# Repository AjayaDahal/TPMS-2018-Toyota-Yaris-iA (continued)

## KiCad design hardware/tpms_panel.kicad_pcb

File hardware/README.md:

# TPMS Monitor Panel: KiCad project

> **Outline accepted from the in-car paper fit (2026-11-09).** The 1:1 template matched the console opening under the HVAC controls, so the board was built to that outline, shrunk by 1 mm on the left, right and bottom edges so it can't come out too big.
> Any small gaps can be closed later with a 3D-printed bezel or chassis.
> `production/tpms_panel_gerbers_jlcpcb.zip` is the order file. The USB holes are Ø25.8 mm, sized for your passthrough sockets' measured 25.16 mm (M25-class) thread.
> The latest design audit is in [docs/design_audit.md](docs/design_audit.md).

This is the hardware for the 315 MHz TPMS display described in the project report
([../TPMS_project_report_ECE6723.pdf](../TPMS_project_report_ECE6723.pdf)). The board outline and front
layout follow Figure 3.6 of the report. The whole project is generated by a script, so you can
change the dimensions and rebuild it (see section 7).

| Front (display side) | Back (electronics) |
|---|---|
|  |  |

## 1. Review: will the documented receiver (MX-05V / XY-MK-5V) work?

**The sensor.** The FCC report in your appendix is for the GM/Schrader **EG53MA4** (FCC ID MRXEG53MA4). These are the four sensors installed in the car's tyres; the Yaris iA's own TPMS is indirect and uses no wheel sensors. Key specs:
- 315 MHz ±70 kHz, **ASK/OOK**, Manchester coded.
- Half-bit pulses are about **123 µs**, so roughly 8 kBd on air and ~4 kbit/s of data.
- Each frame lasts 13–28 ms.
- It sends every 30–60 s while the wheels turn, and nothing while the car is parked unless you trigger it with the LF relearn tool.

At 3 m the FCC measured a peak field strength of 78.4 dBµV/m, which is about −49 dBm into an isotropic antenna. Inside a car you can expect roughly −60 to −80 dBm. That is plenty for both receivers, so sensitivity is not the problem. The real limits are listed below.

| | MX-05V superregenerative (documented) | CC1101 module (purchased) |
|---|---|---|
| Modulation | OOK only | OOK/ASK, 2-FSK, GFSK, 4-FSK, MSK. Also covers the FSK sensors used by Toyota, Ford and many aftermarket brands |
| Selectivity | Very wide (MHz-range) front end. Key fobs and any nearby 300–330 MHz traffic get through | Programmable RX filter (e.g. 203 kHz) and a crystal-referenced synthesizer |
| Frequency stability | Tuned by a trimmer coil that drifts with temperature and vibration (car interior: −20…+70 °C) | Crystal accurate (tens of ppm) |
| Idle output | No squelch, so the DATA pin outputs constant noise. The MCU must reject it all the time | Carrier-sense/RSSI available on GDO2, so the MCU can ignore idle noise |
| ~123 µs Manchester | Marginal: these modules are designed for slow (a few kbit/s) remotes, and the LM358 slicer distorts short pulses | Handled easily |
| Supply / logic | 5 V | 3.3 V only (1.8–3.6 V, not 5 V tolerant) |

**Verdict: the MX-05V is not suitable for the in-car panel. Use the CC1101.**
- On the bench it can be a proof of concept with your GM sensors, but only if it is the **315 MHz** version; the 433 MHz one won't hear them.
- In the car, expect missed and corrupted frames, for the reasons in the table above.
- The PCB keeps an optional, unpopulated socket for it (J3, with R9/R10 as a 5 V→3.3 V divider), only for a side-by-side comparison. Leave J3, R9 and R10 empty.

**Your actual module (from the photos): EBYTE E07-M1101D(-SMA) V2.0**
- **Nothing is missing.** The E07 has an 8-pin 2×4 header and all 8 pins are present; pin 1 is the square pad. The green 10-pin CC1101 boards only add a second VCC and GND.
- **The PCB already fits it.** EBYTE's pin table (1 GND, 2 VCC, 3 GDO0, 4 CSN, 5 SCK, 6 MOSI, 7 MISO, 8 GDO2) and size (15 × 30 mm without the SMA) match the U1 footprint, so the PCB needs no change.
- **It is the 433 MHz build.**
  - The silkscreen says "433M" and EBYTE rates the module for 387–464 MHz.
  - The CC1101 chip tunes to 300–348 MHz, so it can receive the 315 MHz sensors. However, the RF matching parts between the chip and the SMA are tuned for 433 MHz, so it loses some sensitivity at 315 MHz (rough estimate: up to ~10 dB).
  - It should still work. The car gives about −60 to −80 dBm (see above), and the CC1101 needs roughly −100 dBm at this data rate (EBYTE quotes −108 dBm at 0.6 kbps).
- **Use a 315 MHz antenna.** An antenna sold with a 433 MHz module is also tuned for 433 MHz. A 315 MHz SMA whip, or for a quick test a ~23 cm wire on the SMA centre pin, recovers part of the loss. Keep the antenna away from metal. An SMA extension cable lets you put it behind plastic trim and keeps its weight off the module's header in a vibrating car.
- **Bring-up checks:**
  1. Continuity from pin 1 to the SMA outer shell should beep (GND).
  2. Over SPI, read the VERSION status register (0x31, sent as 0xF1).
     - 0x14 (current) or 0x04 (legacy) means a TI CC1101.
     - 0x17 or 0x03 means a known clone chip; RadioLib accepts these and they usually work.
     - 0x00 or 0xFF means the wiring/SPI is wrong.
  3. Check that every tyre's frames arrive with an RSSI well above the idle noise floor, and compare against your RTL-SDR running rtl_433.
- **About "TI" and "clone":** TI makes only the chip. The module is EBYTE's own Chinese design, so a Chinese board is expected and does not by itself mean a fake. Check 2 shows whether the chip is genuine.
- **If the rear tyres drop out:**
  - Use a module built for 315 MHz, or re-tune its RF parts to the 315 MHz values in TI's CC1101 reference design.
  - If the replacement's pinout differs from the E07, wire it to the **J2** 1×8 breakout (GND 3V3 GDO0 CSN SCK MOSI MISO GDO2) instead of U1.

## 2. Microcontroller: ESP32 (DOIT ESP32 DEVKIT V1, 30-pin)

| | Arduino Nano | STM32 Blue Pill | **ESP32 DevKit V1** |
|---|---|---|---|
| Logic level | 5 V (needs level shifters for CC1101 and OLED) | 3.3 V | **3.3 V**, matches CC1101 and OLED |
| RAM | 2 KB, which can't even hold the 4 KB 128×64×4-bit OLED frame buffer | 20 KB | **520 KB** |
| CPU | 16 MHz AVR | 72 MHz M3 | **2×240 MHz** (decoding + UI) |
| Wireless | none | none | **Wi-Fi + BLE**: phone app, OTA updates, logging |
| Notes | | clone MCUs common, needs ST-Link | USB bootloader, hardware pulse counter for the encoder, enough GPIO for display, LEDs and expansion |

Both DOIT variants are sold: **0.9 in (22.86 mm)** and **1.0 in (25.4 mm)** row spacing. The footprint provides both GPIO23…3V3 rows. Populate only the row that matches your board.

## 3. Board summary

- **Outline:**
  - Trapezoid, 189 mm wide at the top, 121 mm at the bottom and 128 mm tall. That is the console opening the paper template matched in the car (191 × 123 × 129 mm), minus 1 mm on the left, right and bottom edges.
  - **USB cable slot** in the right edge: 8 mm wide, 8 mm deep, centred 34 mm below the top. The cable from the car's own USB port, which ends up behind the panel, comes out through it.
  - Two Ø25.8 mm cut-outs for the panel-mount USB passthroughs (measured thread 25.16 mm, M25 class), plus 4× M3 holes.
    - No parts within Ø38 mm on either side of each hole, so an M25 nut (typically 35–37 mm across corners) sits flat. DRC checks this.
    - No tracks within Ø31 mm, so a hole could still be drilled out to Ø30 mm.
    - The mounting holes are placeholders; move or delete them in `panel_config.py`.
  - The shape started as a scale-up of Figure 3.6 (using the 82 mm-wide display as the reference). It was then checked in the car with the 1:1 paper template, and a caliper span along the left trim agreed with it.
- **Front:**
  - NHD-2.7-12864WDW3 OLED (SSD1322, 4-wire SPI).
  - 4× 5 mm tyre LEDs centred under the display in a 2×2 "car" layout (FL FR / RL RR) with a car outline on the silkscreen between them.
  - EC11 rotary encoder with push switch to the right of the display: rotate = up/down, push = OK. BACK is a menu entry on the screen and/or a long-press.
  - The original 4-button layout (UP/OK/DOWN/BACK in a column on the right) is still available: set `INPUT_STYLE = "buttons"` in `scripts/panel_config.py` and rebuild.
- **Back:**
  - ESP32 DevKit (on sockets).
  - CC1101 module on the left, with its SMA connector pointing down so the antenna can go straight back into the console pocket.
  - 12 V ACC input: PTC fuse, ±22 V TVS (SMAJ22CA) and SS34 reverse diode, then a TSR 1-2450 5 V switcher, then an AMS1117 3.3 V LDO with a copper heatsink pour (feeds the OLED and radio).
  - Buzzer driver, optional MX-05V socket, optional CC1101 breakout, I²C/GPIO expansion header.
- **PCB:** 2 layers, 1.6 mm, 1 oz copper, GND pour on both sides with stitching vias, tented vias. Rules: 0.25 mm signal / 0.6 mm power tracks, 0.2 mm clearance, 0.6/0.3 mm vias. DRC also enforces JLCPCB's silkscreen limits (text ≥ 1.0 mm high, ≥ 0.15 mm stroke), via ring ≥ 0.15 mm and hole-to-hole ≥ 0.45 mm.
- **Checks (KiCad 10.0.7):**
  - ERC: 0 errors / 0 warnings.
  - DRC: 0 errors / 0 warnings / 0 unconnected.
  - Schematic ↔ PCB parity: 0 issues.
  - The exported Gerber/drill files were also re-read with an independent parser: outline closed (189 × 128 mm, with the 8 mm cable slot), every plated hole has a pad on both layers, no copper on non-plated holes. See [docs/design_audit.md](docs/design_audit.md).

### ESP32 pin map

| GPIO | Net | Connected to |
|---|---|---|
| IO18 / IO23 / IO19 | SPI_SCK / SPI_MOSI / SPI_MISO | CC1101 and OLED (shared VSPI bus; the OLED is write-only) |
| IO5 | CC_CS | CC1101 CSn |
| IO34 | CC_GDO0 | CC1101 GDO0: demodulated OOK data (use an edge interrupt) |
| IO35 | CC_GDO2 | CC1101 GDO2: e.g. carrier sense |
| IO15 / IO27 / IO26 | OLED_CS / OLED_DC / OLED_RES | NHD pins 17 / 4 / 16 |
| IO25 / IO33 / IO32 / IO14 | LED_FL / FR / RL / RR | LEDs through 220 Ω (active high) |
| IO16 / IO17 / IO4 | ENC_A / ENC_B / ENC_SW | Encoder A/B through 10 k pull-up + 10 k / 10 nF RC filter (use the ESP32 PCNT unit or interrupts); push switch with 10 k pull-up + 100 nF (active low) |
| IO13 | BUZZER | MMBT3904 driving a 5 V buzzer (active high) |
| IO36 | MX05_DATA | Optional MX-05V through a 1 k / 10 k divider (its LM358 output reaches only ~3.0–3.7 V, so this gives 2.7–3.4 V) |
| IO21 / IO22 | I2C_SDA / I2C_SCL | J4 expansion, 4.7 k pull-ups |
| IO2 | IO2_EXP | J4 spare. Keep it low or floating at reset so flashing still works |
| IO39 | IO39_EXP | J4 spare, input-only (ADC1), e.g. a fifth button or a light sensor |

IO12 (boot-strapping pin), IO0, TX0/RX0 and EN are deliberately left unused.

## 4. Ordering at JLCPCB

1. Upload **`production/tpms_panel_gerbers_jlcpcb.zip`**. It contains Gerbers, separate PTH/NPTH Excellon drill files and drill maps.
   - If `DIMENSIONS_CONFIRMED` is ever set back to `False`, the build names the zip `..._DRAFT_dims_unconfirmed.zip` instead. Don't order a DRAFT zip.
2. Options:
   - 2 layers, 1.6 mm, 1 oz.
   - **PCB colour: Black, silkscreen: White** (to match the render). ENIG looks nicer on a front panel than HASL.
   - Via covering: Tented.
   - "Remove order number": **Specify a location**. The `JLCJLCJLCJLC` marker is already on the back silkscreen, so the front stays clean.
3. The board is larger than 100×100 mm, so the low-cost promo price doesn't apply.

`production/tpms_panel_bom.csv` lists every part with suggested part numbers. Lines marked "optional" are only needed for the MX-05V test, the alternative CC1101 wiring, or future expansion.

## 5. Assembly notes

1. **Back, SMD first:** 1206 R/C, SOT-223, SMA, SOD-123, SOT-23, 1812 fuse, 6.3 mm electrolytic, and the C5 tantalum (case A). **C5 is polarized:** its banded end is "+" and goes on pad 1, the end closed off by the silkscreen bracket.
2. **Back, through-hole:**
   - TSR 1-2450 (U3). A substitute must also be a 7805-pinout switcher rated for at least 36 V input, e.g. Mornsun K7805-1000R3 (8–36 V). The RECOM R-78E5.0-1.0 is only rated 8–28 V, so don't use it here.
   - J1 screw terminal and the buzzer.
   - The ESP32 sockets: two 1×15 female headers, in the EN…VIN row plus the GPIO23…3V3 row for your board's width.
   - The CC1101 2×4 female socket.
3. **Front:**
   - LEDs: the square pad is the cathode. The 220 Ω resistors give ~6 mA with red, amber or yellow LEDs. Blue or white LEDs (Vf ≈ 3 V) would only get ~1 mA and look dim; use 47–68 Ω for those.
   - Encoder: EC11 with push switch and a 20 mm D-shaft, fitted with a 20–25 mm knob. Solder the two mounting tabs as well; they take the force when the knob is pushed.
   - Display: 1×20 2.54 mm male header with **pin 1 (VSS, square pad) at the right end when looking at the front** (from the NHD rear-view drawing). If you want the display removable, use a female header.
   - Display hardware: the NHD mounting holes are Ø2.5 mm, so use **M2** screws (M2.5 won't pass through) with **M2 × 3 mm** spacers between the display and the PCB.
4. Before fitting the display, trim the ESP32 socket pins that come through to the front **to ≤ 1 mm**, because they sit under the display.
   - The display's own back carries parts up to ~2.1 mm tall (bezel tabs, FPC connector), and its flex cable runs over the lower socket row.
   - With 3 mm spacers this leaves about 0.9 mm of clearance.
5. The CC1101 module plugs in components-up (facing away from the PCB) with its SMA pointing **down**.
   - In the car, the panel's top edge sits directly under the HVAC controls, so nothing can leave through it. That's why the module was moved off the top-left corner.
   - Fit a **90° SMA adapter** (male–female) on the module and point the 315 MHz antenna straight back into the console pocket.
   - Or use an SMA extension cable (RG316/RG174, 0.3–1 m) to put the antenna somewhere better; see the antenna notes in section 8.
   - The ESP32's micro-USB plug points left toward J2. It has about 60 mm of free run, or about 35 mm if J2 is fitted. A short-bodied or 90° micro-USB cable helps, or flash over Wi-Fi (OTA) once the first firmware is in.
6. **JP1 stays open.** Close it only if you rework the NHD module to jumper option #1 (R4 open, R5 closed) so its OLED boost converter runs from 5 V.
   - At full brightness the OLED draws up to 345 mA (375 mA max) from the 3.3 V LDO, about 0.65 W of heat in U4. The board has a copper pour on U4's tab for this.
   - With option #1, the boost draws ~200 mA from 5 V instead and U4 stays cool. Consider it if the panel will sit in a hot dashboard with a mostly-lit screen.
7. Power:
   - Connect switched **12 V ACC** to J1 (expected draw < 0.5 A).
   - Tap ACC through an **add-a-fuse (1–2 A)** at the fuse box. The on-board PTC protects the board, not the wire.
   - **Never wire it to constant 12 V.** The panel draws about 1 W, which flattens a car battery in roughly two weeks.
   - On the bench, the ESP32's USB alone powers everything. A laptop port (500 mA) can brown out when the screen is bright and Wi-Fi is on, so use a powered hub or a 12 V supply if it resets.
   - Most DevKits have a VBUS diode, so 12 V and USB can be connected together. If yours doesn't, use one or the other.
8. **USB passthroughs:** the two holes take panel-mount USB passthrough cables, with a female socket in front and a male plug behind. They aren't wired to the board.
   - Plug one male end into the car's own USB port behind the panel; the front socket then works like the car's port (phone charging, CarPlay/Android Auto if your head unit has them).
   - Plug the other into a 12 V → USB charger in the car's 12 V socket behind the panel.
     - Use a low-profile ("flush") charger, because a long one sticks out toward the back of the panel.
     - The board's U3 can't power phones, so the charger is needed.
   - The car's ports face the panel. If a straight USB plug or the charger doesn't leave room for the panel to sit flush, use **90° USB-A adapters** (male–female) so the plugs lie flat. Leave some slack so the panel doesn't lever on the car's port.
   - The extension cables are USB 3.0, so they run as USB 2.0 on the car's USB 2.0 port; that's fine.
   - Route both cables down and away from the CC1101 antenna. With a phone connected and charging, the bring-up firmware's noise floor should stay near −100 dBm; if it rises, add clip-on ferrites to the cables near the plugs.
   - Mounting: the thread measures 25.16 mm (M25 class), so the holes are **Ø25.8 mm** (0.6 mm clearance, enough for JLCPCB's ±0.2 mm routing tolerance).
     - Nothing is placed within a Ø38 mm circle on either side, so the nut and flange sit flat.
     - The nearest part is U3 at 19.8 mm from the hole centre, so even a 39 mm nut (across corners) would fit.
   - If the thread binds, ease the hole with a round file (copper-free up to Ø30 mm).
   - The slot in the right edge stays free for an extra cable, such as the antenna extension or the 12 V feed.
9. **First power-up:**
   - Before plugging in the DevKit, CC1101 and display, power the bare board and measure 5 V and 3V3 on the J4 pads.
   - The CC1101's 2×4 header and the DevKit are symmetric, so a module rotated 180° gets reversed power. Check the "1"/"SMA" and "USB"/"ANTENNA" silkscreen first.
   - Then flash the [bring-up firmware](../firmware/bringup/README.md); its self-test checks every part.
10. **For the car (vibration):**
    - Use machined round-pin gold sockets for the DevKit, or solder it in.
    - Put a dab of RTV on the socketed modules.
    - Don't hang a heavy antenna on the module. Use a short stubby antenna on the 90° adapter, or an extension cable with the antenna fixed to the console.
    - Crimp ferrules on the J1 wires.

## 6. Firmware starting points

> The Yaris iA's own TPMS is indirect (ABS wheel speeds, no wheel sensors). The four GM/Schrader EG53MA4 sensors you had installed feed only this panel, so the settings below are the ones to use.
> The [bring-up firmware](../firmware/bringup/README.md) already uses them and decodes the sensors (ID, pressure, temperature). Risks and next steps are in [docs/premortem.md](../docs/premortem.md).

### CC1101 settings for the GM/Schrader EG53MA4

These values are calculated from the CC1101 datasheet formulas for a 26 MHz crystal. Treat them as a starting point and check them in TI SmartRF Studio, which also gives the ASK/OOK AGC settings. The bring-up firmware's OOK profile uses the same settings with a 16 kBd demodulator filter.

| Register | Value | Meaning |
|---|---|---|
| FREQ2/1/0 | 0x0C / 0x1D / 0x8A | 315.000 MHz (793 994 × 26 MHz / 2¹⁶) |
| MDMCFG4 / MDMCFG3 | 0x88 / 0x4B | RX bandwidth 203 kHz, data rate ≈ 8.2 kBd |
| MDMCFG2 | 0x30 | ASK/OOK, no sync word |
| PKTCTRL0 | 0x32 | Asynchronous serial mode |
| IOCFG0 / IOCFG2 | 0x0D / 0x0E | GDO0 = serial data out (to IO34), GDO2 = carrier sense (to IO35) |

How to decode:
1. Timestamp every edge on IO34.
2. Manchester-decode with a half-bit of about 123 µs.
3. Parse the frame as rtl_433's `schrader_EG53MA4` decoder does (`src/devices/schraeder.c`): a 120-bit frame with a 24-bit ID, pressure byte × 25 mbar, temperature byte in °F, and an additive checksum.
4. Trigger each wheel with the OEC-T5 tool to learn which ID belongs to FL/FR/RL/RR.

Libraries such as SmartRC-CC1101-Driver-Lib or RadioLib work on the ESP32.

315 MHz needs band-specific settings besides FREQ:
- TEST0 must be 0x0B below ~323 MHz, versus 0x09 at 433 MHz.
- SmartRC's `setMHZ(315.0)` sets TEST0 and FSCTRL0 for you.
- If you write the registers yourself, export the 315 MHz set from SmartRF Studio. Don't reuse a 433 MHz register dump with only FREQ changed.

Encoder: count A/B with the ESP32 PCNT peripheral (e.g. the ESP32Encoder library); an EC11 gives 4 counts per detent, so divide by 4 for one menu step per click. Use a short press for OK and a long press (~0.6 s) for BACK.

Things to watch in firmware:
- **GDO0 clock at power-up:** until IOCFG0 is written, the CC1101 outputs a 135 kHz clock on GDO0 (its reset default, CLK_XOSC/192). Configure the radio first, then attach the IO34 edge interrupt; otherwise the interrupt floods the CPU.
- **Shared SPI bus:** the CC1101 and the OLED share SCK/MOSI. Keep the CC1101 transactions at ≤ 6.5 MHz (its burst-access limit) and the SSD1322 at ≤ 10 MHz. The CC1101 releases MISO when CSn is high, as long as IOCFG1 stays at its default (0x2E, high impedance).
- **Power loss:** ACC power can drop at any moment. Save learned sensor IDs with NVS (Preferences), and only when they change.
- **Input-only pins:** IO34/35/36/39 have no internal pull-ups. IO36 floats when the optional MX-05V parts are not fitted, so don't enable an interrupt on it then.

## 7. Changing dimensions / regenerating

Everything is generated from three files in `scripts/`:
- `panel_config.py`: outline, front-panel positions (LEDs, encoder or buttons via `INPUT_STYLE`), hole sizes and component placement.
- `design.py`: the circuit (parts, nets, schematic layout).
- `build_tpms_panel.py`: the generator.

Requirements:
- KiCad 10. The build uses `kicad-cli` and the Python that ships with KiCad.
- Java 21 or newer.
- Freerouting 2.5 jar. Set the `FREEROUTING_JAR` environment variable if it isn't in `%LOCALAPPDATA%\Programs\freerouting`.

```powershell
& "$env:LOCALAPPDATA\Programs\KiCad10\bin\python.exe" hardware\scripts\build_tpms_panel.py
#   --no-route   placement only      --no-render  skip 3D renders / STEP
#   --template-only   just rewrite the 1:1 fit template PDF from the current board
```

One run (about 1.5–2 minutes) does all of the following:
- rebuilds the libraries, schematic and project;
- runs ERC;
- places, autoroutes, pours and stitches the board. Freerouting sometimes stalls with one or two connections left, so the script retries with a reshuffled routing order and keeps the best result;
- runs DRC with schematic parity. If any DRC error remains, the script exits with code 2 and prints "do NOT order these Gerbers";
- exports Gerbers, drill files, the zip, BOM, PDFs, renders, the STEP model and the 1:1 fit template.

**Hand edits to `tpms_panel.kicad_pcb` are overwritten** on the next run. Once the dimensions are final you can stop using the script and continue in KiCad.

## 8. Before ordering: checklist

The outline is settled (see "In-car fit" below). What's left before ordering:

1. **USB passthrough sockets: done.** The thread measures **25.16 mm** (caliper, 2026-11-09), so the holes are **Ø25.8 mm** with a Ø38 mm parts-free circle on both sides.
   - Optional: measure the hex nut across its corners. Up to 37 mm fits the parts-free circle as designed, and up to ~39 mm still clears the nearest part (U3).
2. **Optional last check:** print the updated [docs/tpms_panel_fit_template_1to1.pdf](docs/tpms_panel_fit_template_1to1.pdf) at **100 % / Actual size** (check the 100 mm and 4 in bars with a ruler), cut it out and hold it in the console once more.
   - The grey dashed line is the opening it was matched to; the cut line is 1 mm inside it.
   - Feed the car's USB cable through the slot on the right to check the slot position.
   - Push a socket's thread through one of the paper USB holes to check the size.
3. Confirm your ESP32 board is a DOIT 30-pin with an ESP32-WROOM-32 (not WROVER), and whether its rows are 0.9 in or 1.0 in apart. Both widths fit; a 38-pin DevKitC needs a different footprint.
4. Check that the last build said DRC 0 errors / 0 warnings, then upload `production/tpms_panel_gerbers_jlcpcb.zip`.
5. Buy the parts the audit changed: C1 47 µF/50 V (EEE-FK1H470XP), C5 22 µF tantalum case A, D6 SMAJ22CA, R9 1 k.
   - Also buy a 90° SMA adapter (male–female) and a 315 MHz antenna: a short stubby, or a whip on an SMA extension cable.
   - For the USB passthroughs: two 90° USB-A adapters (male–female), and a flush 12 V USB charger if you use the 12 V socket.

### In-car fit (2026-11-09 template photos)

- **Outline:** the printed template matches the console opening under the HVAC controls. The slanted sides follow the carbon-look trims, the top edge sits under the HVAC bezel, and the bottom clears the pocket lip.
  - A caliper span of 117.3 mm along the left trim agrees with the template.
  - No exact measurement set was possible, so the board is the template outline shrunk by **1 mm on the left, right and bottom** (`FIT_CLEARANCE`) and can't be too big.
  - Small gaps can be closed with a 3D-printed bezel/chassis. That printed frame can also hold the board, since the M3 holes are only placeholders.
- **Cable slot (right edge):** 8 mm wide × 8 mm deep, centred 34 mm below the top, level with the car's USB / 12 V strip behind the panel. A cable from there can come out at the side of the panel. With the USB passthroughs it's free for an extra cable; for a thicker cable or plug, widen `NOTCH_R` / `NOTCH_DEPTH`.
- **Depth behind the panel:** the deepest parts are about 16 mm (ESP32 on its sockets, CC1101). The 12 V / USB / AUX strip at the top of the pocket is where it's tightest. If the panel can't sit flush there, the 3D-printed chassis can space it forward.
- **The panel covers the car's 12 V socket, USB, AUX and card slot** (the strip at the top of the pocket). The plan:
  - **Two USB passthrough cables** in the panel's USB holes: one plugs into the car's USB port, the other into a flush 12 V USB charger in the 12 V socket. Use 90° adapters if the plugs need the room; see assembly step 8.
  - The slot in the right edge is free for an extra cable.
  - Power the panel from the 12 V socket's wiring with a fused tap, or from an ACC fuse with an add-a-fuse. The socket should be ACC-switched; check that it reads 0 V with the key off.
- **Antenna:** the old top-left position pointed the SMA connector straight into the HVAC unit, so no antenna or cable could be attached. The radio now sits mid-left with the SMA pointing down; a 90° adapter sends the antenna straight back into the pocket.
  - The console trim is plastic (the carbon look is only a finish), so it doesn't block 315 MHz.
  - Start with a short 315 MHz antenna on the adapter and check each wheel's signal strength with the [bring-up firmware](../firmware/bringup/README.md).
  - If a rear wheel is weaker than about −95 dBm, move the antenna out of the pocket on an extension cable, e.g. up behind the dash or along the console side under plastic. Keep it away from the steel floor tunnel and from the USB socket bodies.
- **Shifter:** in P, the shift knob sits in front of the lower-right part of the panel. A cable plugged into the **right** USB socket may hit it.
  - Check the gap; use a 90° USB cable, or I can move that socket up and left.
  - The display, LEDs and knob stay clear of the shifter.

Already confirmed:
- CC1101 module: an EBYTE E07-M1101D (from your photos). Its pinout and 15 × 30 mm size match U1. It is the 433 MHz build, so expect somewhat lower sensitivity at 315 MHz (see section 1).
- NHD-2.7-12864WDW3: pinout, pin-1 side, header position and hole pattern checked against the current Newhaven datasheet.

## Files

| Path | Content |
|---|---|
| `tpms_panel.kicad_pro / .kicad_sch / .kicad_pcb` | KiCad 10 project |
| `lib/` | Custom symbols (`TPMS.kicad_sym`), footprints (`TPMS.pretty`) and simple 3D models |
| `production/` | Gerber zip for JLCPCB, Gerber/drill folder, BOM |
| `docs/` | Schematic PDF, front-layer PDF, renders, STEP model, 1:1 printable fit template, design audit (`design_audit.md`) |
| `build/` | Intermediate files: netlist, DSN/SES, Freerouting log, ERC/DRC reports (created by the build; not in git) |

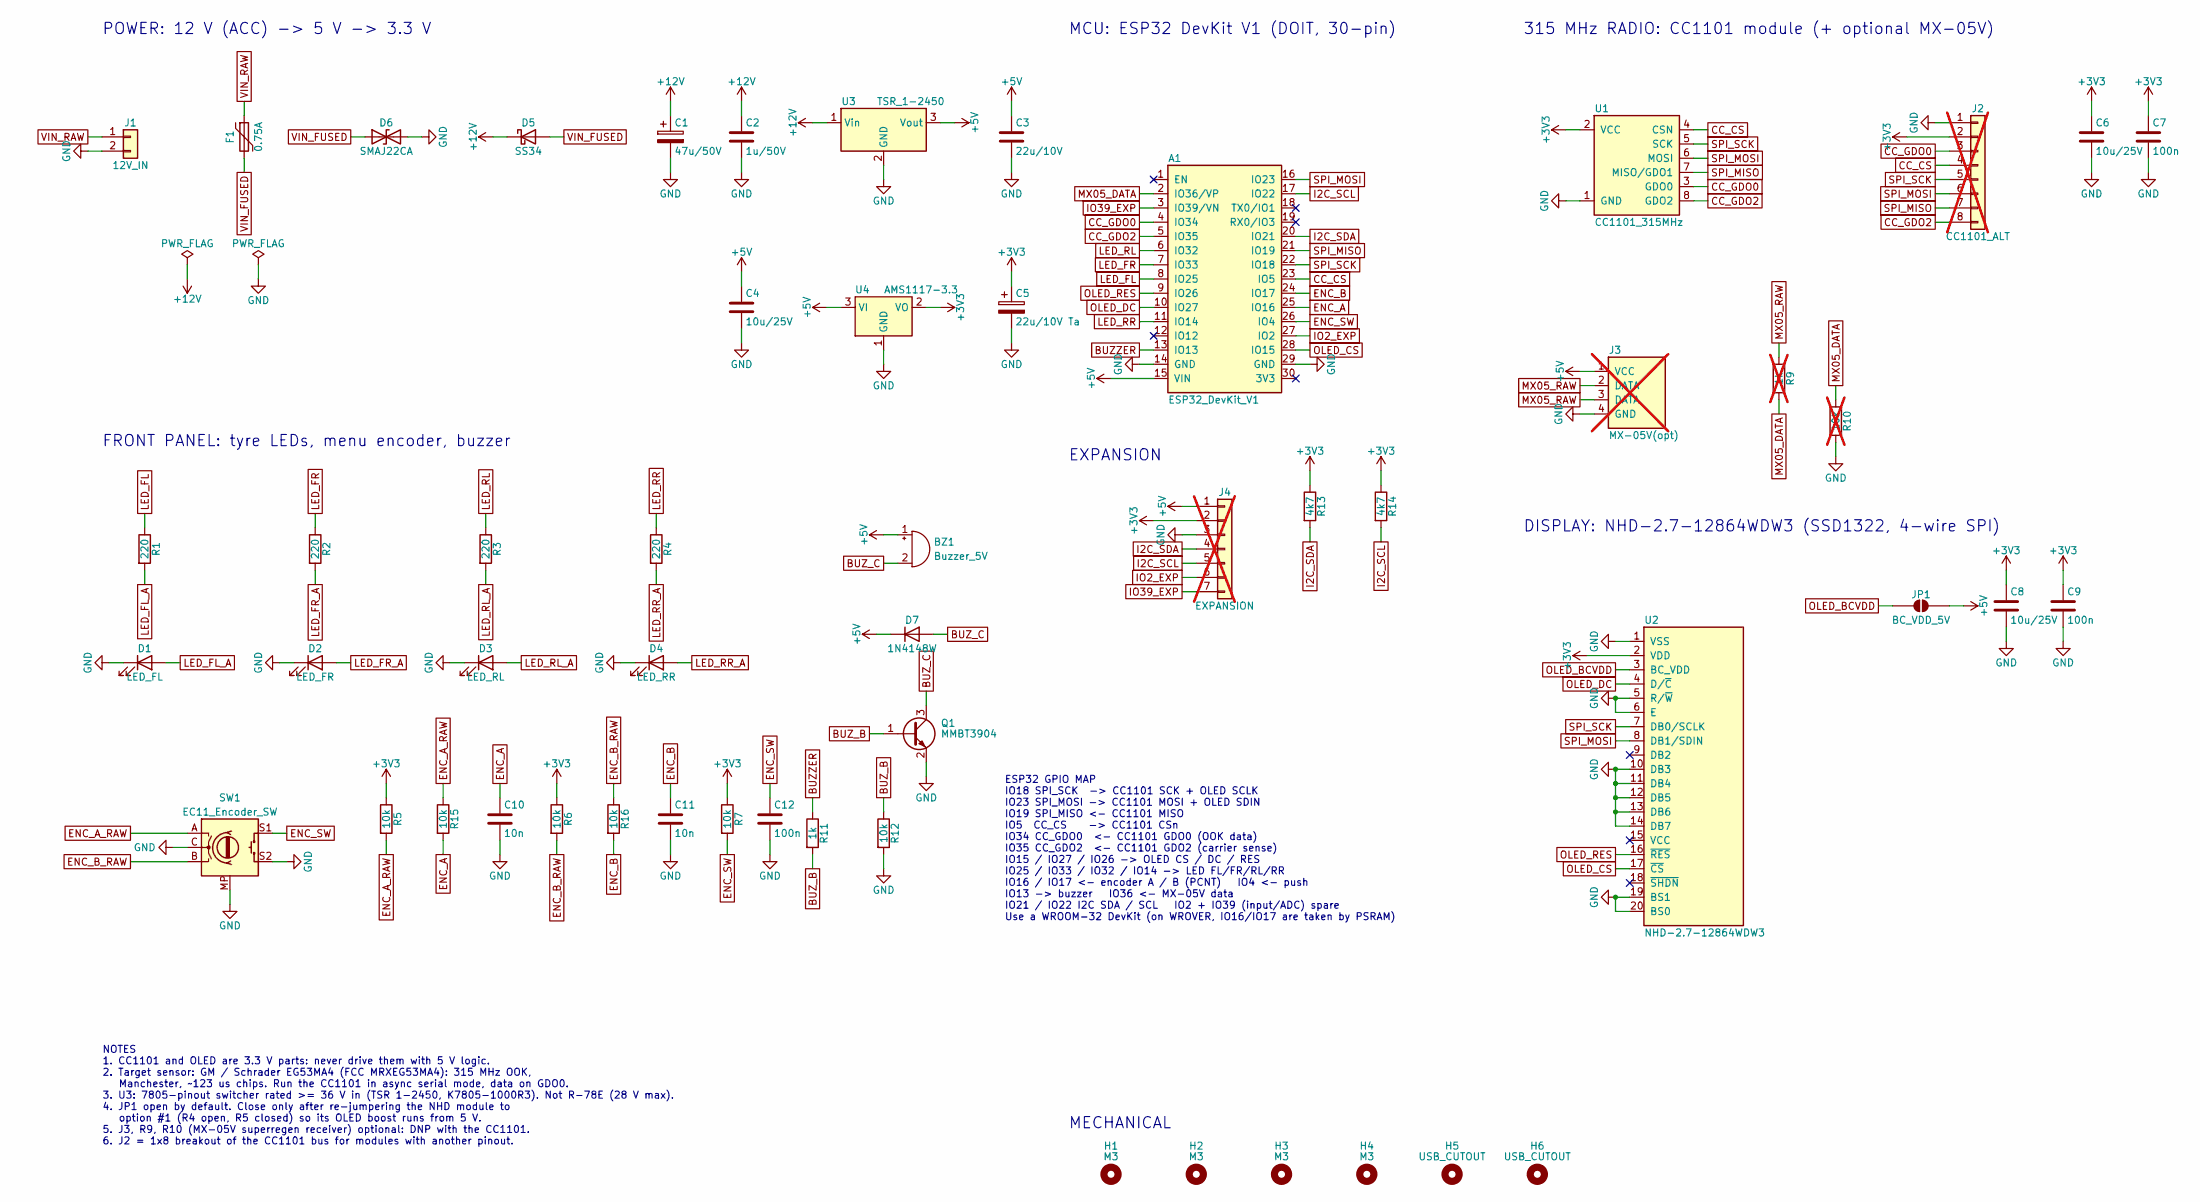
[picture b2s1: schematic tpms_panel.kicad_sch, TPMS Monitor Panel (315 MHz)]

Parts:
A1: ESP32_DevKit_V1; ESP32_DOIT_DevKit_V1_30pin; MPN DOIT ESP32 DEVKIT V1 30-pin + 2x 1x15 2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
BZ1: Buzzer_5V; Buzzer_12x9.5RM7.6; MPN 12 mm 5 V active magnetic buzzer, 7.6 m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
C1: 47u/50V; CP_Elec_6.3x7.7; MPN Panasonic EEE-FK1H470XP
C2: 1u/50V; C_1206_3216Metric
C3: 22u/10V; C_1206_3216Metric
C4, C6, C8: 10u/25V; C_1206_3216Metric
C5: 22u/10V Ta; CP_EIA-3216-18_Kemet-A_HandSolder; MPN KEMET T491A226K010AT
C7, C9, C12: 100n; C_1206_3216Metric
C10, C11: 10n; C_1206_3216Metric
D1: LED_FL; LED_D5.0mm; MPN 5 mm LED
D2: LED_FR; LED_D5.0mm; MPN 5 mm LED
D3: LED_RL; LED_D5.0mm; MPN 5 mm LED
D4: LED_RR; LED_D5.0mm; MPN 5 mm LED
D5: SS34; D_SMA; MPN SS34
D6: SMAJ22CA; D_SMA; MPN Littelfuse SMAJ22CA
D7: 1N4148W; D_SOD-123; MPN 1N4148W
F1: 0.75A; Fuse_1812_4532Metric; MPN Bourns MF-MSMF075/24X-2
H1, H2, H3, H4: M3; MountingHole_3.2mm_M3
H5, H6: USB_CUTOUT; USB_PanelMount_Cutout; MPN USB 3.0 panel-mount passthrough cable, 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
J1: 12V_IN; TerminalBlock_Phoenix_MKDS-1,5-2-5.08_1x02_P5.08mm_Horizont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; MPN Phoenix MKDS 1,5/2-5,08 (1715721)
J2: CC1101_ALT; PinHeader_1x08_P2.54mm_Vertical; MPN 1x8 2.54 mm pin header; not fitted
J3: MX-05V(opt); PinSocket_1x04_P2.54mm_Vertical; MPN 1x4 2.54 mm female header; not fitted
J4: EXPANSION; PinHeader_1x07_P2.54mm_Vertical; MPN 1x7 2.54 mm pin header; not fitted
JP1: BC_VDD_5V; SolderJumper-2_P1.3mm_Open_RoundedPad1.0x1.5mm
Q1: MMBT3904; SOT-23; MPN MMBT3904
R1, R2, R3, R4: 220; R_1206_3216Metric
R5, R6, R7, R12, R15, R16: 10k; R_1206_3216Metric
R9: 1k; R_1206_3216Metric; not fitted
R10: 10k; R_1206_3216Metric; not fitted
R11: 1k; R_1206_3216Metric
R13, R14: 4k7; R_1206_3216Metric
SW1: EC11_Encoder_SW; RotaryEncoder_Alps_EC11E-Switch_Vertical_H20mm; MPN EC11 rotary encoder with push switch (A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
U1: CC1101_315MHz; CC1101_E07-M1101D_Socket; MPN EBYTE E07-M1101D-SMA (CC1101; 433 MHz-t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
U2: NHD-2.7-12864WDW3; MPN Newhaven NHD-2.7-12864WDW3 + 1x20 2.54 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
U3: TSR_1-2450; Converter_DCDC_TRACO_TSR-1_THT; MPN TRACO TSR 1-2450 (6.5-36 V in; alt. Mor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
U4: AMS1117-3.3; SOT-223-3_TabPin2; MPN AMS1117-3.3

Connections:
+3V3: C5.1, C6.1, C7.1, C8.1, C9.1, J2.2, J4.2, R5.1, R6.1, R7.1, R13.1, R14.1, U1.2 (VCC), U2.2 (VDD), U4.2 (VO)
+5V: A1.15 (VIN), BZ1.1 (+), C3.1, C4.1, D7.1 (K), J3.1 (VCC), J4.1, JP1.2 (B), U3.3 (Vout), U4.3 (VI)
+12V: C1.1, C2.1, D5.1 (K), U3.1 (Vin)
BUZZER: A1.13 (IO13), R11.1
BUZ_B: Q1.1 (B), R11.2, R12.1
BUZ_C: BZ1.2 (-), D7.2 (A), Q1.3 (C)
CC_CS: A1.23 (IO5), J2.4, U1.4 (CSN)
CC_GDO0: A1.4 (IO34), J2.3, U1.3 (GDO0)
CC_GDO2: A1.5 (IO35), J2.8, U1.8 (GDO2)
ENC_A: A1.25 (IO16), C10.1, R15.2
ENC_A_RAW: R5.2, R15.1, SW1.A
ENC_B: A1.24 (IO17), C11.1, R16.2
ENC_B_RAW: R6.2, R16.1, SW1.B
ENC_SW: A1.26 (IO4), C12.1, R7.2, SW1.S1
GND: A1.14 (GND), A1.29 (GND), C1.2, C2.2, C3.2, C4.2, C5.2, C6.2, C7.2, C8.2, C9.2, C10.2, C11.2, C12.2, D1.1 (K), D2.1 (K), D3.1 (K), D4.1 (K), D6.2 (A2), J1.2, J2.1, J3.4 (GND), J4.3, Q1.2 (E), R10.2, R12.2, SW1.C, SW1.MP, SW1.S2, U1.1 (GND), U2.1 (VSS), U2.5 (R/~W), U2.6 (E), U2.10 (DB3), U2.11 (DB4), U2.12 (DB5), U2.13 (DB6), U2.14 (DB7), U2.19 (BS1), U2.20 (BS0), U3.2 (GND), U4.1 (GND)
I2C_SCL: A1.17 (IO22), J4.5, R14.2
I2C_SDA: A1.20 (IO21), J4.4, R13.2
IO2_EXP: A1.27 (IO2), J4.6
IO39_EXP: A1.3 (IO39/VN), J4.7
LED_FL: A1.8 (IO25), R1.1
LED_FL_A: D1.2 (A), R1.2
LED_FR: A1.7 (IO33), R2.1
LED_FR_A: D2.2 (A), R2.2
LED_RL: A1.6 (IO32), R3.1
LED_RL_A: D3.2 (A), R3.2
LED_RR: A1.11 (IO14), R4.1
LED_RR_A: D4.2 (A), R4.2
MX05_DATA: A1.2 (IO36/VP), R9.2, R10.1
MX05_RAW: J3.2 (DATA), J3.3 (DATA), R9.1
OLED_BCVDD: JP1.1 (A), U2.3 (BC_VDD)
OLED_CS: A1.28 (IO15), U2.17 (~CS)
OLED_DC: A1.10 (IO27), U2.4 (D/~C)
OLED_RES: A1.9 (IO26), U2.16 (~RES)
SPI_MISO: A1.21 (IO19), J2.7, U1.7 (MISO/GDO1)
SPI_MOSI: A1.16 (IO23), J2.6, U1.6 (MOSI), U2.8 (DB1/SDIN)
SPI_SCK: A1.22 (IO18), J2.5, U1.5 (SCK), U2.7 (DB0/SCLK)
VIN_FUSED: D5.2 (A), D6.1 (A1), F1.2
VIN_RAW: F1.1, J1.1

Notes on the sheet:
POWER: 12 V (ACC) -> 5 V -> 3.3 V
MCU: ESP32 DevKit V1 (DOIT, 30-pin)
315 MHz RADIO: CC1101 module (+ optional MX-05V)
DISPLAY: NHD-2.7-12864WDW3 (SSD1322, 4-wire SPI)
FRONT PANEL: tyre LEDs, menu encoder, buzzer
EXPANSION
MECHANICAL
ESP32 GPIO MAP IO18 SPI_SCK -> CC1101 SCK + OLED SCLK IO23 SPI_MOSI -> CC1101 MOSI + OLED SDIN IO19 SPI_MISO <- CC1101 MISO IO5 CC_CS -> CC1101 CSn IO34 CC_GDO0 <- CC1101 GDO0 (OOK data) IO35 CC_GDO2 <- CC1101 GDO2 (carrier sense) IO15 / IO27 / IO26 -> OLED CS / DC / RES IO25 / IO33 / IO32 / IO14 -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
NOTES 1. CC1101 and OLED are 3.3 V parts: never drive them with 5 V logic. 2. Target sensor: GM / Schrader EG53MA4 (FCC MRXEG53MA4): 315 MHz OOK, Manchester, ~123 us chips. Run the CC1101 in async serial mode, data on GDO0. 3. U3: 7805-pinout switcher rated >= 36 V in (TSR 1-2450, K7805-1000R3). No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

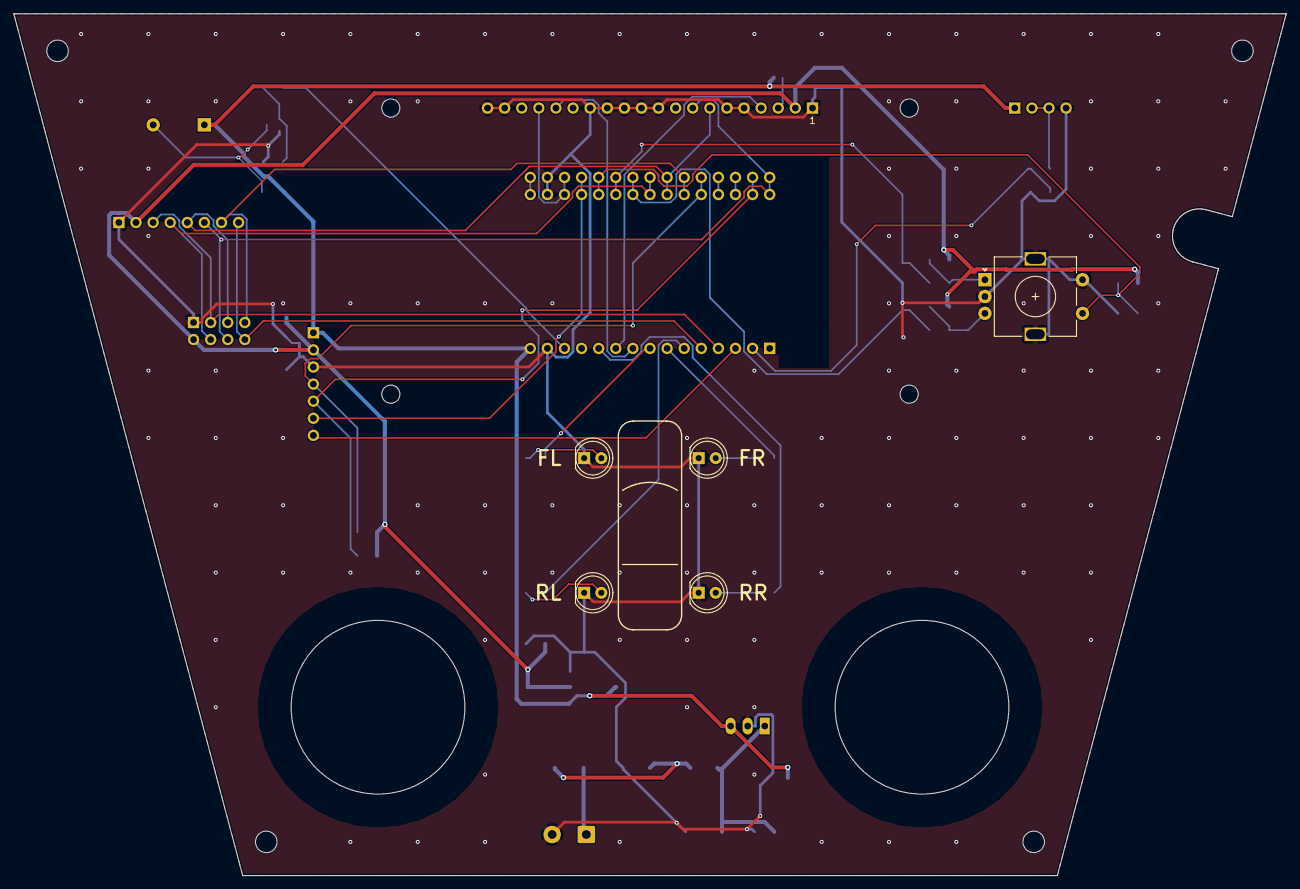
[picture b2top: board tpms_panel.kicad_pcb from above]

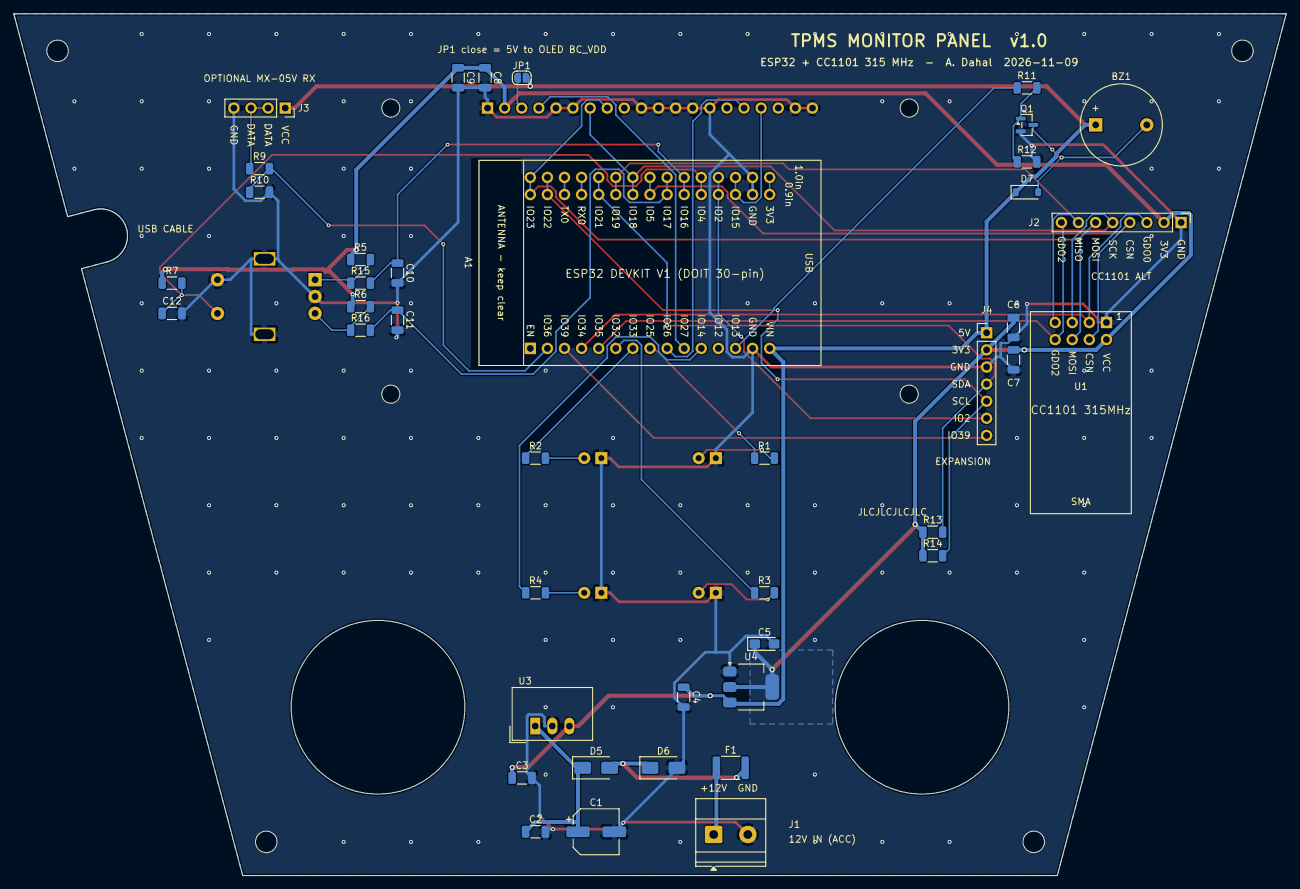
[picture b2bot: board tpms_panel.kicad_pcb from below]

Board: 2 copper layers, 189.0 x 128.0 mm, 54 parts (42 on the bottom side), 38 nets.

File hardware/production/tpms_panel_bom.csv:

Designators,Qty,Value,Footprint,Part / suggestion,Description,Populate
A1,1,ESP32_DevKit_V1,ESP32_DOIT_DevKit_V1_30pin,DOIT ESP32 DEVKIT V1 30-pin + 2x 1x15 2.54 mm female header,ESP32 dev board (0.9 in or 1.0 in row spacing),yes
BZ1,1,Buzzer_5V,Buzzer_12x9.5RM7.6,"12 mm 5 V active magnetic buzzer, 7.6 mm pitch",Low-pressure alarm,yes
C1,1,47u/50V,CP_Elec_6.3x7.7,Panasonic EEE-FK1H470XP,"Aluminium electrolytic 47 uF 50 V, 6.3 mm (U3 needs 22 uF / 50 V at its input above 30-32 V)",yes
C2,1,1u/50V,C_1206_3216Metric,,MLCC X7R 1206,yes
C3,1,22u/10V,C_1206_3216Metric,,MLCC X5R 1206,yes
C4 C6 C8,3,10u/25V,C_1206_3216Metric,,MLCC X5R 1206,yes
C5,1,22u/10V Ta,CP_EIA-3216-18_Kemet-A_HandSolder,KEMET T491A226K010AT,"Tantalum 22 uF 10 V case A: AMS1117 output, as its datasheet specifies for stability",yes
C7 C9 C12,3,100n,C_1206_3216Metric,,MLCC X7R 1206,yes
C10 C11,2,10n,C_1206_3216Metric,,MLCC X7R 1206,yes
D1 D2 D3 D4,4,LED_FL / LED_FR / LED_RL / LED_RR,LED_D5.0mm,5 mm LED,Tyre status LEDs,yes
D5,1,SS34,D_SMA,SS34,"Schottky 40 V 3 A, reverse-polarity protection",yes
D6,1,SMAJ22CA,D_SMA,Littelfuse SMAJ22CA,"Bidirectional TVS 22 V, SMA: 24.4 V min breakdown (24 V jump start), 35.5 V clamp (< 36 V of U3)",yes
D7,1,1N4148W,D_SOD-123,1N4148W,Flyback diode,yes
F1,1,0.75A,Fuse_1812_4532Metric,Bourns MF-MSMF075/24X-2,"PTC fuse 1812, 0.75 A hold (0.49 A at 70 C), 24 V",yes
H1 H2 H3 H4,4,M3,MountingHole_3.2mm_M3,,M3 mounting hole,board feature (no part)
H5 H6,2,USB_CUTOUT,USB_PanelMount_Cutout,"USB 3.0 panel-mount passthrough cable, female socket to male plug, M25-class thread (measured 25.2 mm), ~30 cm (buy 2)","Cut-out for a panel-mount USB passthrough: front socket, male plug behind goes to the car's USB port / a 12 V USB charger",board cut-out; part bought separately
J1,1,12V_IN,"TerminalBlock_Phoenix_MKDS-1,5-2-5.08_1x02_P5.08mm_Horizontal","Phoenix MKDS 1,5/2-5,08 (1715721)","Screw terminal, 12 V ACC input",yes
J2,1,CC1101_ALT,PinHeader_1x08_P2.54mm_Vertical,1x8 2.54 mm pin header,Breakout for CC1101 modules with other pinouts,optional
J3,1,MX-05V(opt),PinSocket_1x04_P2.54mm_Vertical,1x4 2.54 mm female header,Optional MX-05V / XY-MK-5V 315 MHz receiver,optional
J4,1,EXPANSION,PinHeader_1x07_P2.54mm_Vertical,1x7 2.54 mm pin header,Future expansion: I2C + spare GPIO,optional
JP1,1,BC_VDD_5V,SolderJumper-2_P1.3mm_Open_RoundedPad1.0x1.5mm,,Close for display jumper option #1,board feature (no part)
Q1,1,MMBT3904,SOT-23,MMBT3904,Buzzer driver,yes
R1 R2 R3 R4,4,220,R_1206_3216Metric,,1206 1%,yes
R5 R6 R7 R12 R15 R16,6,10k,R_1206_3216Metric,,1206 1%,yes
R9,1,1k,R_1206_3216Metric,,1206 1%,optional
R10,1,10k,R_1206_3216Metric,,1206 1%,optional
R11,1,1k,R_1206_3216Metric,,1206 1%,yes
R13 R14,2,4k7,R_1206_3216Metric,,1206 1%,yes
SW1,1,EC11_Encoder_SW,RotaryEncoder_Alps_EC11E-Switch_Vertical_H20mm,"EC11 rotary encoder with push switch (ALPS EC11E-switch type), 20 mm D-shaft + 20-25 mm knob","Menu knob: rotate = up/down, push = OK",yes
U1,1,CC1101_315MHz,CC1101_E07-M1101D_Socket,EBYTE E07-M1101D-SMA (CC1101; 433 MHz-tuned build works at 315 MHz with some loss) + 2x4 2.54 mm female header + 315 MHz antenna,Sub-GHz transceiver used as OOK receiver,yes
U2,1,NHD-2.7-12864WDW3,NHD-2.7-12864WDW3,Newhaven NHD-2.7-12864WDW3 + 1x20 2.54 mm header + 4x M2 screws/nuts + 4x M2 x 3 mm spacers,"2.7 in 128x64 OLED, 4-wire SPI",yes
U3,1,TSR_1-2450,Converter_DCDC_TRACO_TSR-1_THT,"TRACO TSR 1-2450 (6.5-36 V in; alt. Mornsun K7805-1000R3, 8-36 V)","5 V 1 A switching regulator, 7805 pinout, needs >= 36 V input rating",yes
U4,1,AMS1117-3.3,SOT-223-3_TabPin2,AMS1117-3.3,3.3 V 1 A LDO (display + radio),yes

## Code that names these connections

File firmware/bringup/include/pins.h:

#pragma once
// Pin map of the TPMS panel PCB. Must match hardware/scripts/design.py (the ESP32 pin nets).

// Shared VSPI bus: CC1101 + OLED (the OLED is write-only)
constexpr int PIN_SPI_SCK = 18;
constexpr int PIN_SPI_MISO = 19;
constexpr int PIN_SPI_MOSI = 23;

// CC1101 module (U1 / J2)
constexpr int PIN_CC_CS = 5;
constexpr int PIN_CC_GDO0 = 34;   // input-only: demodulated data in asynchronous serial mode
constexpr int PIN_CC_GDO2 = 35;   // input-only: carrier sense

// NHD-2.7-12864WDW3 OLED (SSD1322, 4-wire SPI)
constexpr int PIN_OLED_CS = 15;
constexpr int PIN_OLED_DC = 27;
constexpr int PIN_OLED_RES = 26;

// Tyre LEDs, active high through 220 ohm
constexpr int PIN_LED_FL = 25;
constexpr int PIN_LED_FR = 33;
constexpr int PIN_LED_RL = 32;
constexpr int PIN_LED_RR = 14;

// EC11 encoder: 10 k pull-ups + RC filters on the board, active low
constexpr int PIN_ENC_A = 16;
constexpr int PIN_ENC_B = 17;
constexpr int PIN_ENC_SW = 4;

constexpr int PIN_BUZZER = 13;     // active high, MMBT3904 low-side switch, 5 V active buzzer
constexpr int PIN_MX05_DATA = 36;  // input-only: optional MX-05V through R9/R10 (floats if not fitted)

constexpr int PIN_I2C_SDA = 21;    // J4 expansion
constexpr int PIN_I2C_SCL = 22;

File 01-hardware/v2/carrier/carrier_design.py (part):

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C("C215", "100n", "3V3", "GND")
D("D203", "SMBJ6.0CA", "5V_PI", "GND", fp=SMB, sym="Device:D_TVS",
  desc="Overvoltage clamp (Preferred): a shorted buck blows F101 instead of the Pi")
R("R214", "22k", "5V_PI", "PI_PGOOD", desc="Rail-up sense to GPIO15: 3.1 V when 5V_PI is up")
R("R215", "33k", "PI_PGOOD", "GND")
R("R216", "1k", "5V_PI", "LEDPI_A")
LED("D204", "green", "GND", "LEDPI_A", desc="5V_PI present")
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# Turn-signal and AUX inputs: 12 V through 2.4 k, an indicator LED and the opto's LED (~4 mA at 12.6 V,
# ~15 mA at a 40 V load dump); 1N4148W across both LEDs against reverse voltage. The return pin is separate
# (twisted pair to a ground near the lamp); a DNP 0 R ties it to board GND.
for side, n, gpio, base in (("L", 0, "ESP_IO36", 501), ("R", 1, "ESP_IO39", 506)):
    p = f"BLK{side}_"
    R(f"R{base}", "1.2k", p + "IN", p + "1", fp=R0805)
    R(f"R{base + 1}", "1.2k", p + "1", p + "2", fp=R0805)
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part("J4", "Connector_Generic_MountingPin:Conn_01x04_MountingPin", "GH-4", GH4,
     {"1": "POD_BTN", "2": "GND", "3": "POD_BUZP", "4": "POD_BUZN", "MP": "GND"},
     desc="BUZ: 12 V piezo (3 +, 4 -); 1-2 spare button input (IO4)")
for side, n, gpio in (("L", 0, "ESP_IO25"), ("R", 1, "ESP_IO14")):
    b = 601 + 4 * n
    NFET(f"Q{601 + n}", "AO3400A", f"LED{side}_G", "GND", f"LED{side}_K", desc=f"{side} door LED, low side, PWM")
    R(f"R{b}", "100", gpio, f"LED{side}_G")
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     desc="Piezo feed PTC, after the 12 V shunt: the INA226 at 0x40 sees a shorted piezo lead")
D("D601", "1N4148W", "POD_BUZP", "POD_BUZN")
NFET("Q604", "AO3400A", "FAN_G", "GND", "FAN_N", desc="Lid fan, on by default")
R("R611", "10k", "3V3", "FAN_G", desc="Fan on while the expander pin is an input (power-up default)")
R("R612", "1k", "EXP_P1", "FAN_G")
D("D602", "1N4148W", "5V_ESP", "FAN_N")
part("J8", "Connector_Generic:Conn_01x02", "FAN", HDR1x2RA, two("5V_ESP", "FAN_N"), hand=True,
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# ================================================================== 7xx: CC1101 radio
part("A2", "TPMS2:CC1101_Module", "CC1101_315MHz", FP_CC1101,
     {"1": "GND", "2": "3V3_RF", "3": "CC_GDO0", "4": "CC_CSN", "5": "SPI_SCK", "6": "SPI_MOSI", "7": "CC_MISO",
      "8": "CC_GDO2"}, hand=True, desc="CC1101 module (2x4 E07 / V2.0 pinout) on a socket")
part("FB701", "Device:FerriteBead", "600R@100MHz", FB0603, two("3V3", "3V3_RF"))
C("C701", "10u", "3V3_RF", "GND")
C("C702", "100n", "3V3_RF", "GND")
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R("R703", "33", "CC_GDO2", "ESP_IO35")
part("J10", "Connector_Generic:Conn_01x08", "CC1101_ALT", HDR1x8,
     {"1": "GND", "2": "3V3_RF", "3": "CC_GDO0", "4": "CC_CSN", "5": "SPI_SCK", "6": "SPI_MOSI", "7": "CC_MISO",
      "8": "CC_GDO2"}, dnp=True, desc="DNP: breakout for a module with another pinout (wire it here)")

# ================================================================== 8xx: I2C peripherals
R("R801", "4.7k", "3V3", "I2C_SDA")
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
# ================================================================== 9xx: Pi link, GPS
# J6 is the whole Pi <-> ESP32 link: UART (Pi UART0 <-> ESP32 UART2), and the Pi's I2C6 (GPIO22/23) switched onto
# the carrier's I2C bus by the Pi's own GPIO18 (PI_AUX_C, also read by the ESP32 on expander P2). Q901 / Q902 are
# the classic bidirectional level-shift switches: gate on GPIO18, source on the Pi side, and R911 / R912 are the
# Pi-side pull-ups, powered by GPIO18 too. With GPIO18 low, or the Pi off, halted or booting, the gates are at 0 V
# and the body diodes face the carrier bus: nothing on the Pi side can pull the ESP32's bus low. I2C6 rather than
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     desc="PI: to the Pi's GPIO pins 6 (GND), 8 (TXD), 10 (RXD), 12 (GPIO18, I2C enable), 15 (GPIO22, SDA6), "
          "16 (GPIO23, SCL6)")
R("R901", "1k", "PI_TXD", "ESP_IO16")
R("R902", "4.7k", "ESP_IO17", "PI_RXD", desc="Limits back-powering the Pi's GPIO while it is off")
R("R903", "1k", "PI_AUX_C", "EXP_P2")
R("R904", "100k", "EXP_P2", "GND", desc="Holds the I2C-enable line (and Q901 / Q902) off while the Pi is off")
NFET("Q901", "2N7002", "PI_AUX_C", "PI_SDA", "I2C_SDA", desc="Pi SDA6 onto the I2C bus while the Pi drives GPIO18 high")
NFET("Q902", "2N7002", "PI_AUX_C", "PI_SCL", "I2C_SCL", desc="Pi SCL6 onto the I2C bus while the Pi drives GPIO18 high")
R("R911", "4.7k", "PI_AUX_C", "PI_SDA", desc="Pi-side SDA pull-up, powered only while GPIO18 is high")
R("R912", "4.7k", "PI_AUX_C", "PI_SCL", desc="Pi-side SCL pull-up, powered only while GPIO18 is high")
part("J7", "Connector_Generic_MountingPin:Conn_01x06_MountingPin", "GH-6", GH6,
     {"1": "GPS_5V", "2": "GPS_RXD_C", "3": "GPS_TXD_C", "4": "GPS_SCL", "5": "GPS_SDA", "6": "GND", "MP": "GND"},
     desc="GPS (Pixhawk port): 5V, TX (to GPS RX), RX (from GPS TX), SCL, SDA, GND")
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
